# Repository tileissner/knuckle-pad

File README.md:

# knuckle-pad

After getting into custom keyboards I was looking to get a gaming keypad to free up mouse space for shooters. Since none of the possible options were 100% what I wanted, were too expensive or simply not available anymore I decided to design my very own keyboard from scratch.

# Rev. 1

In Rev. 1 the Knuckle Pad features a 4x6+5 keys in a ortholinear layout, offering 3 1.25u pinky keys, 4 radially positioned thumb keys and a uniquely positioned key to press with the head of your metacarpal bone (what I call "inner knuckle"). However, after actually using the first prototype the placement of said "knuckle key" turned out to be way to aggresive (too low, felt like it was in the way).

[//]: # (add picture of layout here)

# Rev. 2

Rev. 2 features a top-mounted MCU to reduce the overall build height, but sacrifices the keys "5" and "T" for it. Furthermore, I added a slight WASD columnar stagger for better ergonomics and moved the "knuckle key" up to right under the 4th row of the 1st column. 

The 1.25u keys in the 1st col have also been replaced with 1u keys for better keycap profile compatibility. They have been moved to the edge of the PCB to still have these keys separated from the rest and emulate the feeling of a "normal" keyboard.

Rev. 2 also features VIAL support so you can map the keys to your personal preference very easily.

[//]: # (add picture of layout here)

# Pictures

# Q&A:

Q: Why the knuckle key?

A: At some point in time I (unconsciously) developed the habit of using my knuckles to press CTRL when playing shooters as I pressing said key with my pinky fingers felt rather uncomfortable.

[//]: # (Q: How am I gonna flame my team mates with half a keyboard?)

[//]: # (Why the hell do you still use the in-game text chat?)

# Ordering PCBs

# Parts needed

# Future plans

- <del>switch plate</del>
- <del>Bottom plate</del>
- <del>Change to black pill microcontroller</del> (No purpose in doing this anymore as pro micros with usb-c are sufficient for this kb)
- Hot-Swap
- Might design a stacked acrylic case if I'm feeling spicy (not anytime soon though)
- Since I designed this KB after finding out about the free montly prototype that allpcb offered and since I wanted to use that service I was constrained to a maximum PCB area of 15000mm^2. Consequently, I could not have BOTH a top-mounted MCU AND all rows with 6 columns. Allpcb apparently discountinued that service (atleast if you haven't bought any PCBs in the last 6 months from them), so this means that if I'm doing a Rev. 3 I will not be constrained anymore by the max size for free prototypes and can have ALL the keys + a top-mounted MCU.

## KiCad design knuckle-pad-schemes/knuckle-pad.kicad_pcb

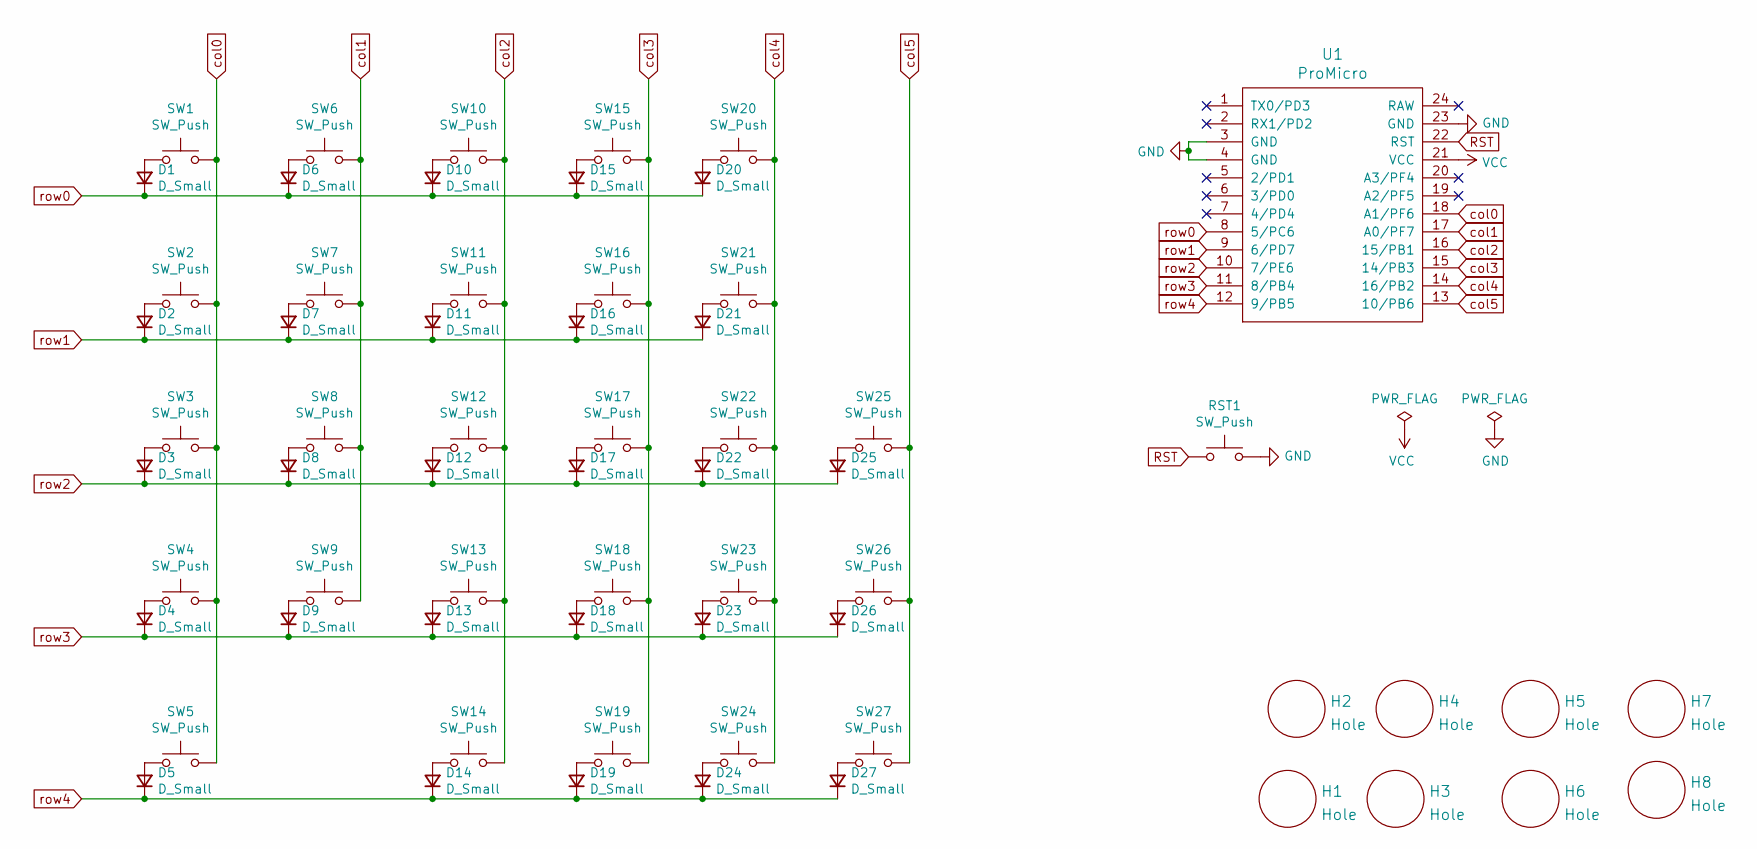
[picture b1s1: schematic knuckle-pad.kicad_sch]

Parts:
D1, D2, D3, D4, D5, D6, D7, D8, D9, D10, D11, D12, D13, D14, D15, D16, D17, D18, D19, D20, D21, D22, D23, D24, D25, D26, D27: D_Small; D_THT_7.62mm
H1, H2, H3, H4, H5, H6, H7, H8: Hole; M2_HOLE_PCB
RST1: SW_Push; Switch_Reset_THT
SW1, SW2, SW3, SW4, SW5, SW6, SW7, SW8, SW9, SW10, SW11, SW12, SW13, SW14, SW15, SW16, SW17, SW18, SW19, SW20, SW21, SW22, SW23, SW24, SW25, SW26, SW27: SW_Push; MXOnly-1U-NoLED
U1: ProMicro; ArduinoProMicro-ZigZag

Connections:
GND: RST1.2, U1.3 (GND), U1.4 (GND), U1.23 (GND)
unnamed: D1.2 (A), SW1.1
unnamed: D2.2 (A), SW2.1
unnamed: D3.2 (A), SW3.1
unnamed: D4.2 (A), SW4.1
unnamed: D5.2 (A), SW5.1
unnamed: D6.2 (A), SW6.1
unnamed: D7.2 (A), SW7.1
unnamed: D8.2 (A), SW8.1
unnamed: D9.2 (A), SW9.1
unnamed: D10.2 (A), SW10.1
unnamed: D11.2 (A), SW11.1
unnamed: D12.2 (A), SW12.1
unnamed: D13.2 (A), SW13.1
unnamed: D14.2 (A), SW14.1
unnamed: D15.2 (A), SW15.1
unnamed: D16.2 (A), SW16.1
unnamed: D17.2 (A), SW17.1
unnamed: D18.2 (A), SW18.1
unnamed: D19.2 (A), SW19.1
unnamed: D20.2 (A), SW20.1
unnamed: D21.2 (A), SW21.1
unnamed: D22.2 (A), SW22.1
unnamed: D23.2 (A), SW23.1
unnamed: D24.2 (A), SW24.1
unnamed: D25.2 (A), SW25.1
unnamed: D26.2 (A), SW26.1
unnamed: D27.2 (A), SW27.1
RST: RST1.1, U1.22 (RST)
VCC: U1.21 (VCC)
col0: SW1.2, SW2.2, SW3.2, SW4.2, SW5.2, U1.18 (A1/PF6)
col1: SW6.2, SW7.2, SW8.2, SW9.2, U1.17 (A0/PF7)
col2: SW10.2, SW11.2, SW12.2, SW13.2, SW14.2, U1.16 (15/PB1)
col3: SW15.2, SW16.2, SW17.2, SW18.2, SW19.2, U1.15 (14/PB3)
col4: SW20.2, SW21.2, SW22.2, SW23.2, SW24.2, U1.14 (16/PB2)
col5: SW25.2, SW26.2, SW27.2, U1.13 (10/PB6)
row0: D1.1 (K), D6.1 (K), D10.1 (K), D15.1 (K), D20.1 (K), U1.8 (5/PC6)
row1: D2.1 (K), D7.1 (K), D11.1 (K), D16.1 (K), D21.1 (K), U1.9 (6/PD7)
row2: D3.1 (K), D8.1 (K), D12.1 (K), D17.1 (K), D22.1 (K), D25.1 (K), U1.10 (7/PE6)
row3: D4.1 (K), D9.1 (K), D13.1 (K), D18.1 (K), D23.1 (K), D26.1 (K), U1.11 (8/PB4)
row4: D5.1 (K), D14.1 (K), D19.1 (K), D24.1 (K), D27.1 (K), U1.12 (9/PB5)

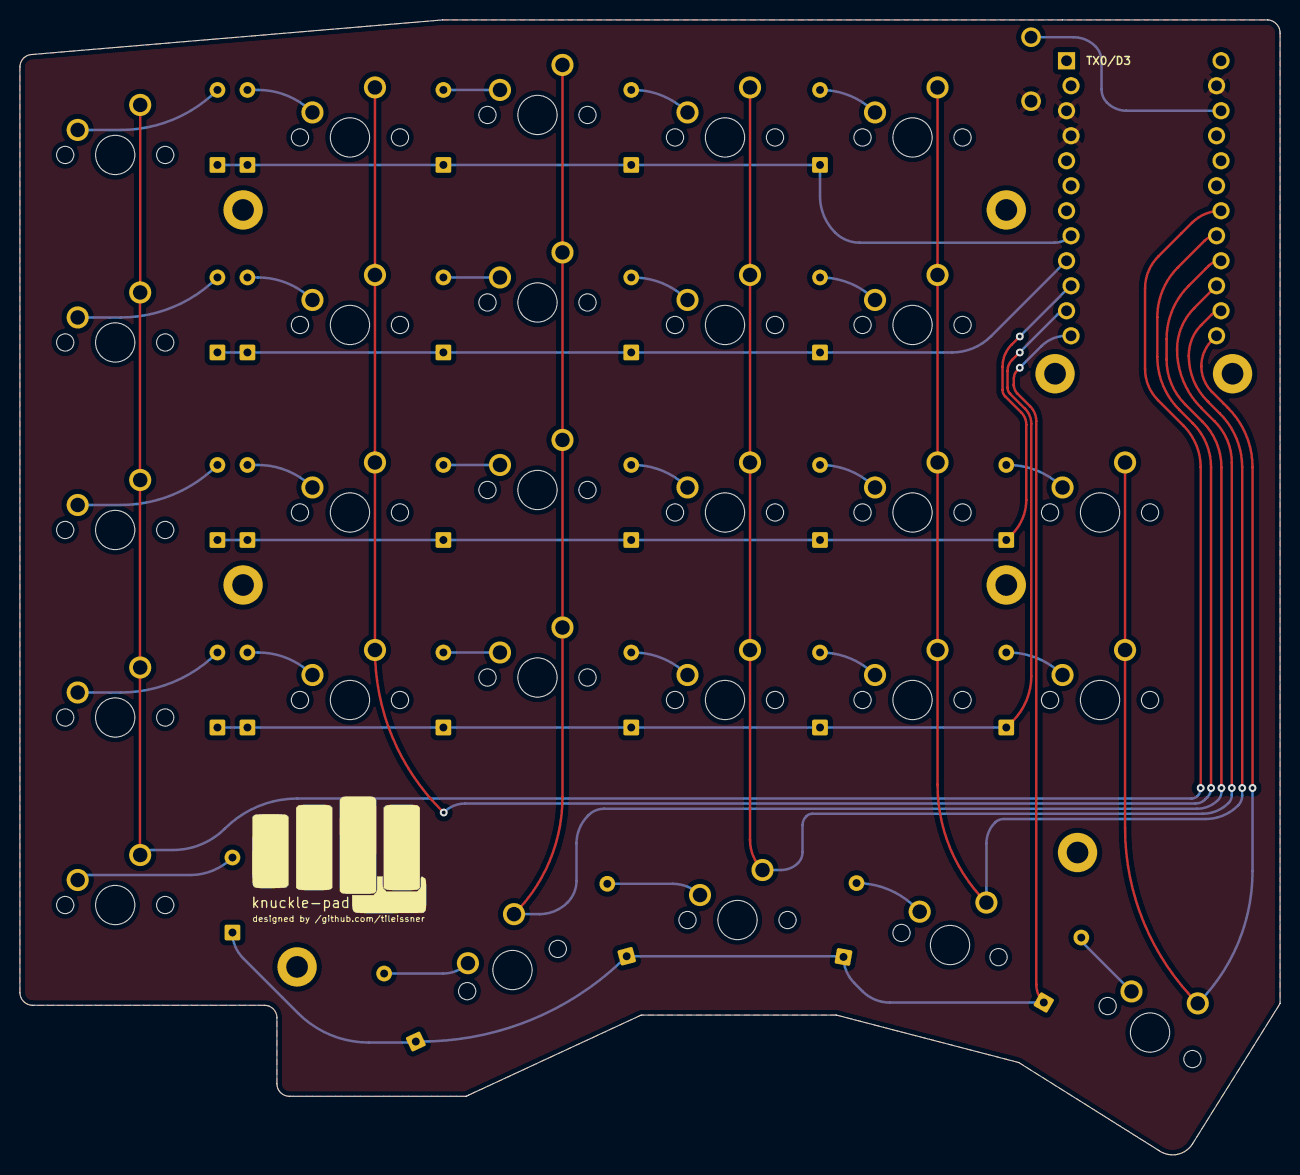
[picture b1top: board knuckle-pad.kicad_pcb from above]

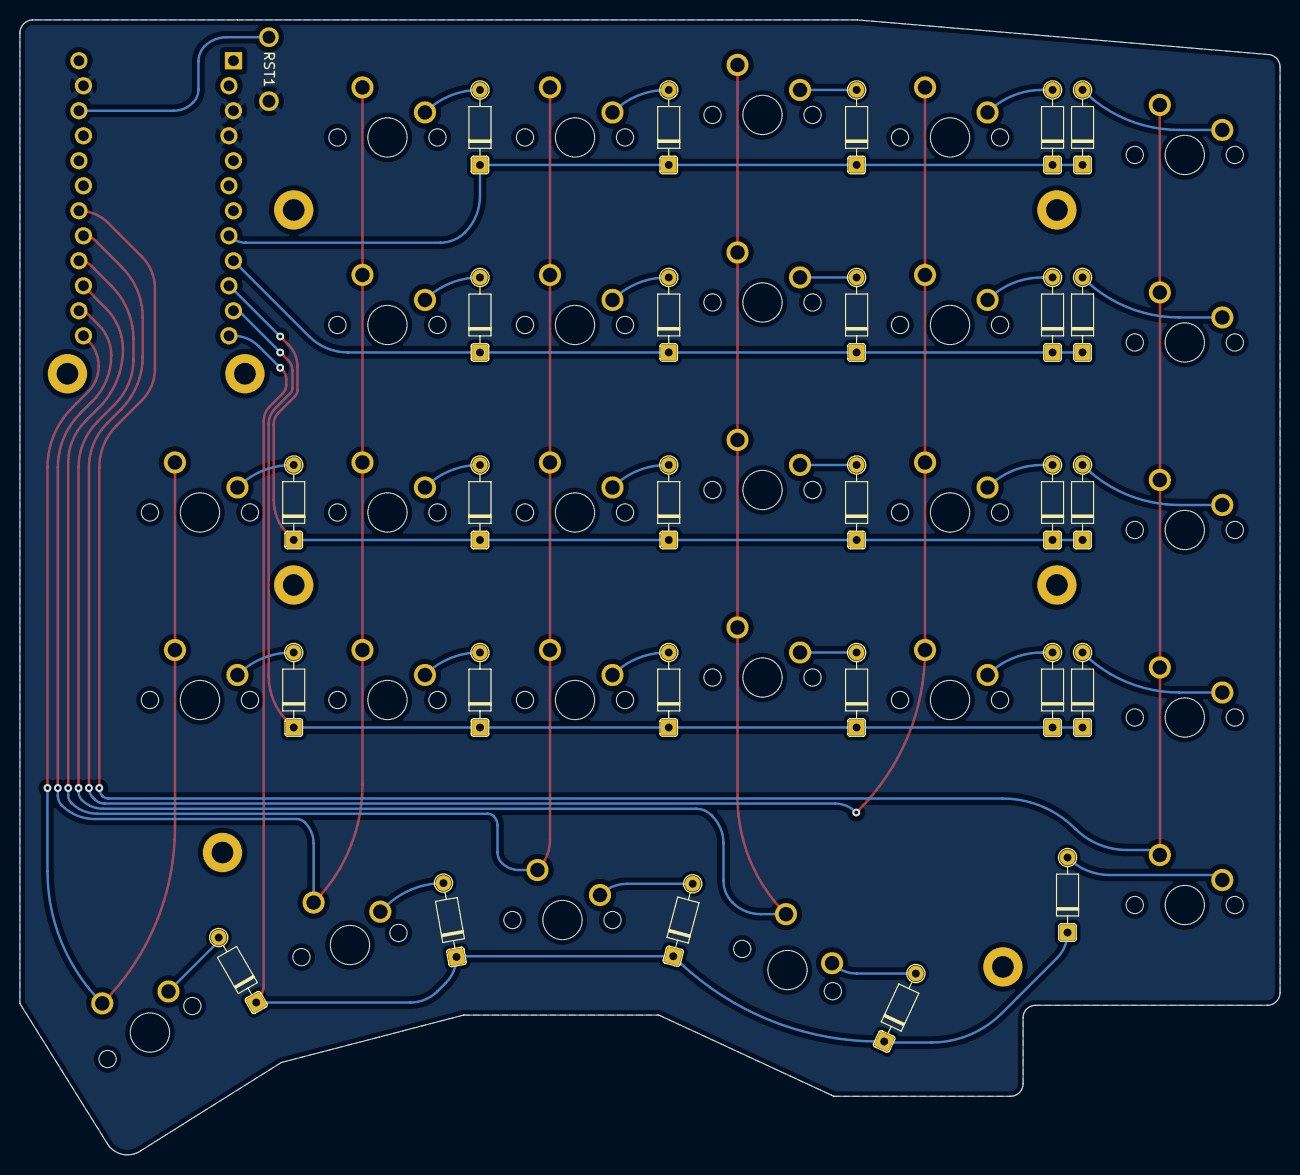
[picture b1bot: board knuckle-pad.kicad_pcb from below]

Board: 2 copper layers, 128.0 x 115.3 mm, 64 parts (28 on the bottom side), 40 nets.

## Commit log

2021-08-20 1st iteration of schemes
2021-08-20 updated pcb shape to (preliminary) final+added pwr_flag to schematic
2021-08-21 push before routing
2021-08-21 rounded all edges(
2021-08-21 added 1st routing, needs optimization
2021-08-22 finished routing
2021-08-22 added logo and finalized routing
2021-08-22 fixed no connect flags
2021-08-23 added ground on copper layers
2021-08-23 changed switch footprint to mx-NoLed ones
2021-08-24 changed mounting hole pos to match plate
2021-08-24 clean up
2021-08-24 add gerbers.zip
2021-08-26 ordered first proto from allpcb
2021-08-28 add switch plate
2021-09-17 v2 started -complete reroute; flipped ProMicro, changed diode footprint
2021-09-19 before changing holes
2021-09-27 complete rework
2021-09-28 prelim version before trying to fit mcu cover and sw plate
2021-09-29 moved mcu and switched back to traymount
2021-09-29 final v2, moved rst to outer edge
2021-09-30 sw plate and mcu cover files
2021-10-01 finalized MCU cover
2021-10-03 finalized sw plate and mcu cover design
2021-10-04 added via firmware and moved all files to v2 dir
2021-10-05 fixed psycho engraving
2021-10-13 readme
2021-10-13 readme 2
2021-11-04 add case files
2021-11-05 add bugged firmware
2022-12-29 add firmware
